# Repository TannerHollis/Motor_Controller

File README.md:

# Motor_Controller
 Full Bridge Controller for DC-DC or DC Motors

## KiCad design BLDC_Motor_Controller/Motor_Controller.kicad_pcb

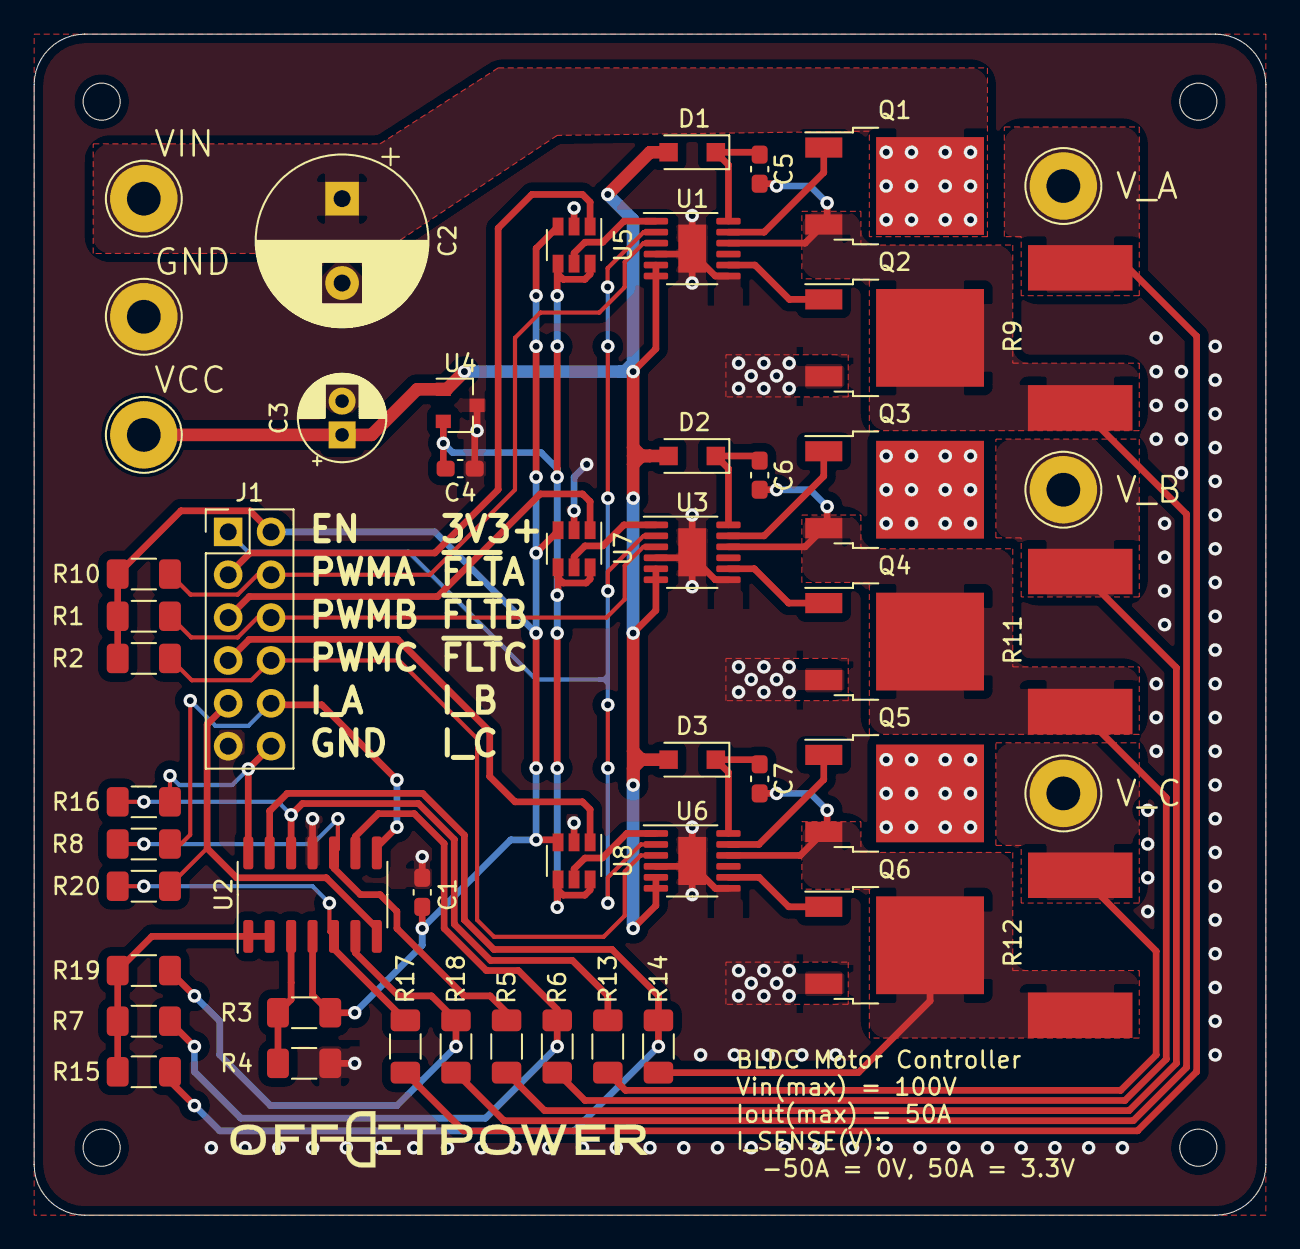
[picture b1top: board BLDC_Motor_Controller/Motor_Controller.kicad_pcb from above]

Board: 2 copper layers, 73.0 x 70.0 mm, 55 parts (0 on the bottom side), 41 nets.

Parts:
C1, C4: 100N; C_0603_1608Metric_Pad1.08x0.95mm_HandSolder
C2: 100U; CP_Radial_D10.0mm_P5.00mm
C3: 10U; CP_Radial_D5.0mm_P2.00mm
C5, C6, C7: 220N; C_0603_1608Metric_Pad1.08x0.95mm_HandSolder
D1, D2, D3: D_Schottky; D_SOD-123F
H1, H2, H3, H4: MountingHole; MountingHole_2.2mm_M2
J1: I/O; PinHeader_2x06_P2.54mm_Vertical
J2, J3, J4, J5, J6, J7: PowerTab; TestPoint_THTPad_D4.0mm_Drill2.0mm
Q1, Q2, Q3, Q4, Q5, Q6: FDD86250-F085‎; TO-252-2
R1, R2, R10: 51K; R_1206_3216Metric_Pad1.30x1.75mm_HandSolder
R3, R4: 100K; R_1206_3216Metric_Pad1.30x1.75mm_HandSolder
R5, R6, R13, R14, R17, R18: 1K; R_1206_3216Metric_Pad1.30x1.75mm_HandSolder
R7, R8, R15, R16, R19, R20: 17K4; R_1206_3216Metric_Pad1.30x1.75mm_HandSolder
R9, R11, R12: 2L; CSS2H-3920K-2L00FE_Small_Outline
U1, U3, U6: LTC7060IMSE; MSOP-12-1EP_3x4mm_P0.65mm_EP1.65x2.85mm
U2: LM2902; SOIC-14_3.9x8.7mm_P1.27mm
U4: RT9064-50GV; SOT-23
U5, U7, U8: PI4ULS5V201TAEX; SOT-23-6

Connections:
1V65_REF: R7.1, R15.1, R19.1, U2.1, U2.2
+3V3: C1.1, J1.2, R1.2, R2.2, R3.1, R10.2, U2.4, U5.3, U7.3, U8.3
+5V: C4.2, U4.2, U5.4, U5.6, U7.4, U7.6, U8.4, U8.6
CSR_A+: C5.2, Q1.3, Q2.2, R9.2, R18.2, U1.10
CSR_A-: J5.1, R9.1, R17.2
CSR_B+: C6.2, Q3.3, Q4.2, R6.2, R11.2, U3.10
CSR_B-: J6.1, R5.2, R11.1
CSR_C+: C7.2, Q5.3, Q6.2, R12.2, R14.2, U6.10
CSR_C-: J7.1, R12.1, R13.2
EN: J1.1, U1.2, U3.2, U6.2
GND: C1.2, C2.2, C3.2, C4.1, J1.11, J4.1, Q2.3, Q4.3, Q6.3, R4.2, U1.4, U1.7, U1.13, U2.11, U3.4, U3.7, U3.13, U4.3, U5.2, U6.4, U6.7, U6.13, U7.2, U8.2
I_SENSE_A: J1.9, R20.1, U2.7
I_SENSE_B: J1.10, R8.1, U2.8
I_SENSE_C: J1.12, R16.1, U2.14
unnamed: C5.1, D1.1, U1.12
unnamed: C6.1, D2.1, U3.12
unnamed: C7.1, D3.1, U6.12
unnamed: Q1.1, U1.11
unnamed: Q2.1, U1.8
unnamed: Q3.1, U3.11
unnamed: Q4.1, U3.8
unnamed: Q5.1, U6.11
unnamed: Q6.1, U6.8
unnamed: R3.2, R4.1, U2.3
unnamed: R5.1, R8.2, U2.10
unnamed: R6.1, R7.2, U2.9
unnamed: R13.1, R16.2, U2.12
unnamed: R14.1, R15.2, U2.13
unnamed: R17.1, R20.2, U2.5
unnamed: R18.1, R19.2, U2.6
PWM_A: U1.1, U5.5
PWM_B: U3.1, U7.5
PWM_C: U6.1, U8.5
PWM_IN_A: J1.3, U5.1
PWM_IN_B: J1.5, U7.1
PWM_IN_C: J1.7, U8.1
VCC: C3.1, D1.2, D2.2, D3.2, J3.1, U1.5, U1.6, U3.5, U3.6, U4.1, U6.5, U6.6
Vdrive: C2.1, J2.1, Q1.2, Q3.2, Q5.2
~FLT~_A: J1.4, R10.1, U1.3
~FLT~_B: J1.6, R1.1, U3.3
~FLT~_C: J1.8, R2.1, U6.3

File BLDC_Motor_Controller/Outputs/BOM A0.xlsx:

Bill of Materials
BLDC Motor Controller |  |  |  | Started: September 16th, 2021 Finished:
 |  |  |  | Total | 64 |  | 34.840000000000003
Component | Reference(s) | Value | JLCPCB Code | Digikey Code | Quantity | Cost | Subtotal
Unpolarized capacitor | C1, C4 | 100N |  | 1276-1006-1-ND | 2 | 0.1 | 0.2
Unpolarized capacitor | C2 | 100U |  | 493-7437-1-ND | 1 | 2.04 | 2.04
Unpolarized capacitor | C3 | 10U |  | 732-8411-1-ND | 1 | 0.17 | 0.17
Unpolarized capacitor | C5, C6, C7 | 220N |  | 587-5013-1-ND | 3 | 0.26 | 0.78
Schottky diode | D1, D2, D3 | SL210PL-TP |  | SL210PL-TPMSCT-ND | 3 | 0.43 | 1.29
Mounting Hole without connection | H1, H2, H3, H4 | MountingHole |  |  | 4 |  | 0
Generic connector, double row, 02x06 | J1 | I/O |  |  | 1 |  | 0
Mounting Hole with connection | J2, J3, J4, J5, J6, J7 | PowerTab |  |  | 6 |  | 0
N-Channel MOSFET, 150V, 50A | Q1, Q2, Q3, Q4, Q5, Q6 | FDD86250-F085‎ |  | FDD86250-F085OSCT-ND | 6 | 1.79 | 10.74
Resistor | R1, R2, R10 | 51K |  | 311-51KERCT-ND | 3 | 0.1 | 0.30000000000000004
Resistor | R3, R4 | 100K |  | A129834CT-ND | 2 | 0.1 | 0.2
Resistor | R5, R6, R13, R14, R17, R18 | 1K |  | 13-AC1206DR-071KLCT-ND | 6 | 0.13 | 0.78
Resistor | R7, R8, R15, R16, R19, R20 | 17K4 |  | P17.4KFCT-ND | 6 | 0.1 | 0.60000000000000009
Resistor | R9, R11, R12 | 2L |  | 118-CSS2H-3920K-2L00FECT-ND | 3 | 1.52 | 4.5600000000000005
100V Half-Bridge Driver with Floating Grounds and Adjustable Dead-Time | U1, U3, U6 | LTC7060IMSE |  | 161-LTC7060IMSE#PBF-ND | 3 | 3.03 | 9.09
Low-Power, Quad-Operational Amplifiers, DIP-14/SOIC-14/SSOP-14 | U2 | LM2902 |  | 497-14852-1-ND | 1 | 0.52 | 0.52
Linear Regulator, 5V | U4 | RT9064-50GV |  | 1028-1312-1-ND | 1 | 0.51 | 0.51
Logic Bidirectional Translator | U5, U7, U8 | PI4ULS5V201TAEX |  | AE10812-ND | 3 | 0.46 | 1.3800000000000001
Heat Sink, 19x6mm |  | V5619A |  | AE10812-ND | 3 | 0.36 | 1.08
Thermal Pad |  | TG-A1250-5-5-0.5 |  | 1168-TG-A1250-5-5-0.5-ND | 6 | 0.1 | 0.60000000000000009

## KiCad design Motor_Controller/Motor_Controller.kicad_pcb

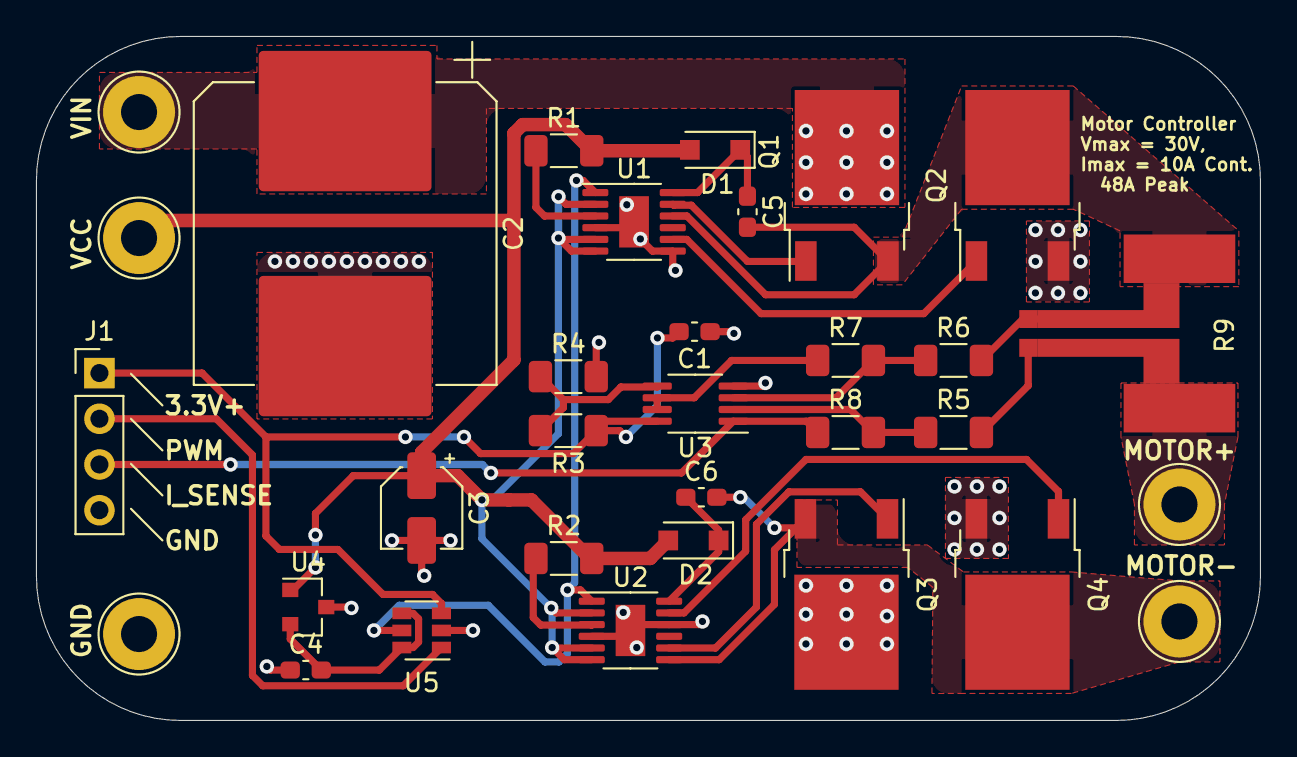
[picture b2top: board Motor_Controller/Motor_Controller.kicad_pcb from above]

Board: 2 copper layers, 68.0 x 38.0 mm, 32 parts (0 on the bottom side), 23 nets.

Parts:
C1, C4: 100N; C_0603_1608Metric_Pad1.08x0.95mm_HandSolder
C2: 470U; CP_Elec_16x22
C3: 10U; CP_Elec_4x5.4
C5, C6: 220N; C_0603_1608Metric_Pad1.08x0.95mm_HandSolder
D1, D2: D_Schottky; D_SOD-123F
J1: I/O; PinHeader_1x04_P2.54mm_Vertical
Q1, Q2, Q3, Q4: DMG4800LK3; TO-252-2
R1, R2: 51K; R_1206_3216Metric_Pad1.30x1.75mm_HandSolder
R3, R4: 100K; R_1206_3216Metric_Pad1.30x1.75mm_HandSolder
R5, R6: 1K; R_1206_3216Metric_Pad1.30x1.75mm_HandSolder
R7, R8: 17K4; R_1206_3216Metric_Pad1.30x1.75mm_HandSolder
R9: 2L; CSS2H-3920K-2L00FE
TP1, TP2, TP3, TP4, TP5: PowerTab; TestPoint_THTPad_D4.0mm_Drill2.0mm
U1, U2: LTC7060IMSE; MSOP-12-1EP_3x4mm_P0.65mm_EP1.65x2.85mm
U3: LM358; MSOP-8_3x3mm_P0.65mm
U4: RT9064-50GV; SOT-23
U5: PI4ULS5V201TAEX; SOT-23-6

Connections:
+3V3: C1.1, J1.1, R3.1, U3.8, U5.3
+5V: C4.2, U4.2, U5.4, U5.6
CSR+: C5.2, Q1.3, Q2.2, R6.2, R9.2, U1.10
CSR-: R5.2, R9.1, TP1.1
GND: C1.2, C2.2, C3.2, C4.1, J1.4, Q2.3, Q4.3, R4.2, TP4.1, U1.4, U1.7, U1.13, U2.4, U2.10, U2.13, U3.4, U4.3, U5.2
I_SENSE: J1.3, R8.1, U3.1
unnamed: C5.1, D1.1, U1.12
unnamed: C6.1, D2.1, U2.12
unnamed: C6.2, Q3.3, Q4.2, TP2.1, U2.7
unnamed: Q1.1, U1.11
unnamed: Q2.1, U1.8
unnamed: Q3.1, U2.8
unnamed: Q4.1, U2.11
unnamed: R1.1, U1.3
unnamed: R2.1, U2.3
unnamed: R3.2, R4.1, U3.5
unnamed: R5.1, R8.2, U3.2
unnamed: R6.1, R7.2, U3.3
unnamed: R7.1, U3.6, U3.7
PWM: U1.1, U2.1, U5.5
PWM_IN: J1.2, U5.1
VCC: C3.1, D1.2, D2.2, R1.2, R2.2, TP3.1, U1.2, U1.5, U1.6, U2.2, U2.5, U2.6, U4.1
Vdrive: C2.1, Q1.2, Q3.2, TP5.1

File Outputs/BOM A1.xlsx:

Bill of Materials
Motor Controller |  |  |  | Started: September 7th, 2021 Finished:
 |  |  |  | Total | 29 |  | 21.599999999999998
Component | Reference(s) | Value | JLCPCB Code | Digikey Code | Quantity | Cost | Subtotal
Unpolarized capacitor | C1, C4 | 100N |  | 1276-1006-1-ND | 2 | 0.1 | 0.2
Unpolarized capacitor | C2 | 470U |  | 493-7437-1-ND | 1 | 2.04 | 2.04
Unpolarized capacitor | C3 | 10U |  | 732-8411-1-ND | 1 | 0.17 | 0.17
Unpolarized capacitor, 100V | C5, C6 | 220N |  | 587-5013-1-ND | 2 | 0.26 | 0.52
Schottky diode, 100V 2A | D1, D2 | SL210PL-TP |  | SL210PL-TPMSCT-ND | 2 | 0.43 | 0.86
Generic connector, single row, 01x07 | J1 | I/O |  |  | 1 |  | 0
N-Channel MOSFET 100V, 70A | Q1, Q2, Q3, Q4 | FDD86250-F085‎ |  | FDD86250-F085OSCT-ND | 4 | 1.79 | 7.16
Resistor | R1, R2 | 51K |  | 311-51KERCT-ND | 2 | 0.1 | 0.2
Resistor | R3, R4 | 100K |  | A129834CT-ND | 2 | 0.1 | 0.2
Resistor | R5, R6 | 1K |  | 13-AC1206DR-071KLCT-ND | 2 | 0.13 | 0.26
Resistor | R7, R8 | 17K4 |  | P17.4KFCT-ND | 2 | 0.1 | 0.2
Resistor | R9 | 2L |  | 118-CSS2H-3920K-2L00FECT-ND | 1 | 1.52 | 1.52
100V Half-Bridge Driver with Floating Grounds and Adjustable Dead-Time | U1, U2 | LTC7060IMSE |  | 161-LTC7060IMSE#PBF-ND | 2 | 3.03 | 6.06
Low-Power, Dual Operational Amplifiers, DIP-8/SOIC-8/TO-99-8 | U3 | LM358AWST |  | 497-14852-1-ND | 1 | 0.52 | 0.52
LDO 5V Regulator | U4 | RT9064-50GV |  | 1028-1312-1-ND | 1 | 0.51 | 0.51
Logic Translator | U5 | PI4ULS5V201TAEX |  | PI4ULS5V201TAEXCT-ND | 1 | 0.46 | 0.46
Heat Sink, 19x6mm |  | V5619A |  | AE10812-ND | 2 | 0.36 | 0.72

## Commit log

2021-09-07 Init Commit
    Unfinished Design
2021-09-15 Updated Motor Controller
    Added 100V Functionality, Changed MOSFET (100V, 70A), Changed Diode (100V 2A), Changed Capacitor (100V 100uF, D10mm, P5mm) and changed to in-stock op-amp LM358AWST
2021-09-15 Revved Up
    Added schematic Rev1 pdf
2021-09-15 Updated bootstrap Cap to 100V
    Forgot to upgrade bootstrapping capacitor to 100V as well...
2021-09-17 Added BLDC Motor Controller
    Divided Project between AC and DC motor controllers. AC motor features three current sensors - even though ya only need two - to facilitate space vector control, torque control, FOC control or V/f co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
2021-09-22 Updated design
    Added outputs with BOM
